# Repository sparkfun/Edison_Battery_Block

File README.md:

SparkFun Block for Intel Edison - Battery/Power
=================================================

[*SparkFun Block for Intel Edison - Battery/Power (DEV-13037)*](https://www.sparkfun.com/products/13037)

Go wireless with Edison!  
The Battery board brings a single cell LiPo Charger and 400mah battery to power an Intel Edision and expansion cards.  
The Battery board can be used with an external battery to increase runtime.  Simply plug in a micro USB cable to charge.  
The power switch removes the battery from the Edison while allowing it to charge via the microUSB cable.

Repository Contents
-------------------
* **/Hardware** - Eagle design files (.brd, .sch)
* **/Production** - Production panel files (.brd)

Documentation
--------------
* **[Hookup Guide](https://learn.sparkfun.com/tutorials/sparkfun-blocks-for-intel-edison---battery-block)** - Basic hookup guide for the battery/power block.
* **[SparkFun Fritzing repo](https://github.com/sparkfun/Fritzing_Parts)** - Fritzing diagrams for SparkFun products.
* **[SparkFun 3D Model repo](https://github.com/sparkfun/3D_Models)** - 3D models of SparkFun products. 

Product Versions
----------------
* [Battery Block](https://www.sparkfun.com/products/13037)- Battery block.
* [Power Block](https://www.sparkfun.com/products/13727)- Battery block without lipo battery installed. 

License Information
-------------------

This product is _**open source**_! 

Please review the LICENSE.md file for license information. 

If you have any questions or concerns on licensing, please contact techsupport@sparkfun.com.

Distributed as-is; no warranty is given.

- Your friends at SparkFun.

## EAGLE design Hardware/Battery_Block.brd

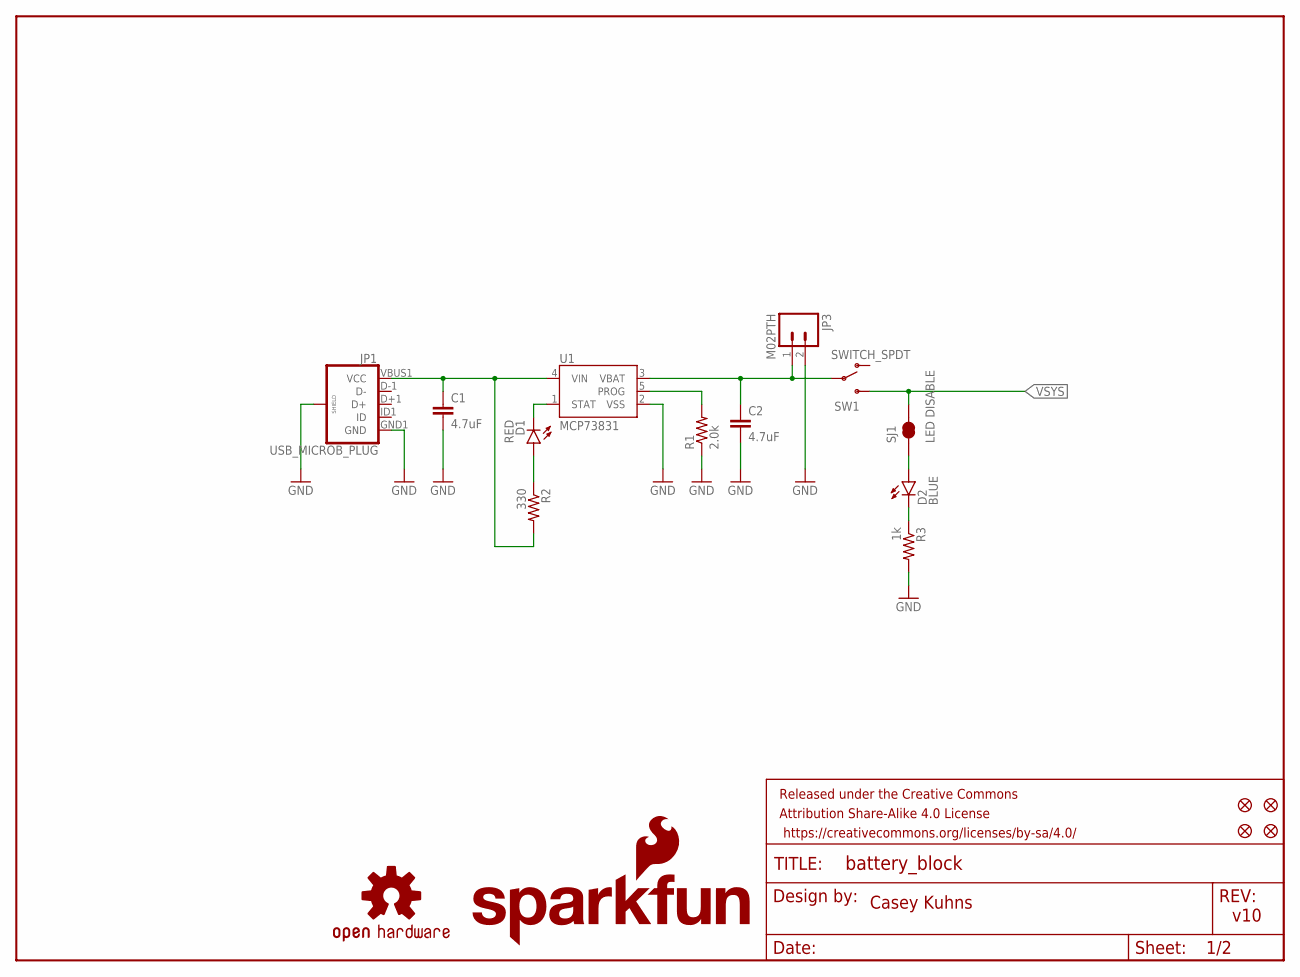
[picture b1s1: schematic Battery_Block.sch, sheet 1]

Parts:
C1, C2: 4.7uF; 0603-CAP
D1: RED; LED-0603
D2: BLUE; LED-0603
FID1, FID2, FID3, FID4: FIDUCIAL1X2; FIDUCIAL-1X2
FRAME1: FRAME-LETTER; CREATIVE_COMMONS
JP1: USB_MICROB_PLUG; USB-B-MICRO-SMD_V03
JP3: M02PTH; 1X02
LOGO1: OSHW-LOGOS; OSHW-LOGO-S
LOGO4: SFE_LOGO_NAME_FLAME.1_INCH; SFE_LOGO_NAME_FLAME_.1
R1: 2.0k; 0603-RES
R2: 330; 0603-RES
R3: 1k; 0603-RES
SJ1: LED DISABLE; PAD-JUMPER-2-NC_BY_TRACE_YES_SILK
SW1: SWITCH_SPDT; KPS-1290
U1: MCP73831; SOT23-5

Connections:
GND: C1.2, C2.2, JP1.GND1 (GND), JP1.SHIELD1 (SHIELD), JP1.SHIELD2 (SHIELD), JP1.SHIELD3 (SHIELD), JP3.2, R1.1, R3.2, U1.2 (VSS); also elsewhere on the board
unnamed: D2.C, R3.1
unnamed: R1.2, U1.5 (PROG)
unnamed: D1.A, R2.1
unnamed: D1.C, U1.1 (STAT)
unnamed: D2.A, SJ1.1
VBAT: C2.1, JP3.1, SW1.P, U1.3 (VBAT)
VIN: C1.1, JP1.VBUS1 (VCC), R2.2, U1.4 (VIN)
VSYS: SJ1.2, SW1.S; also elsewhere on the board

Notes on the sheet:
Casey Kuhns
v10

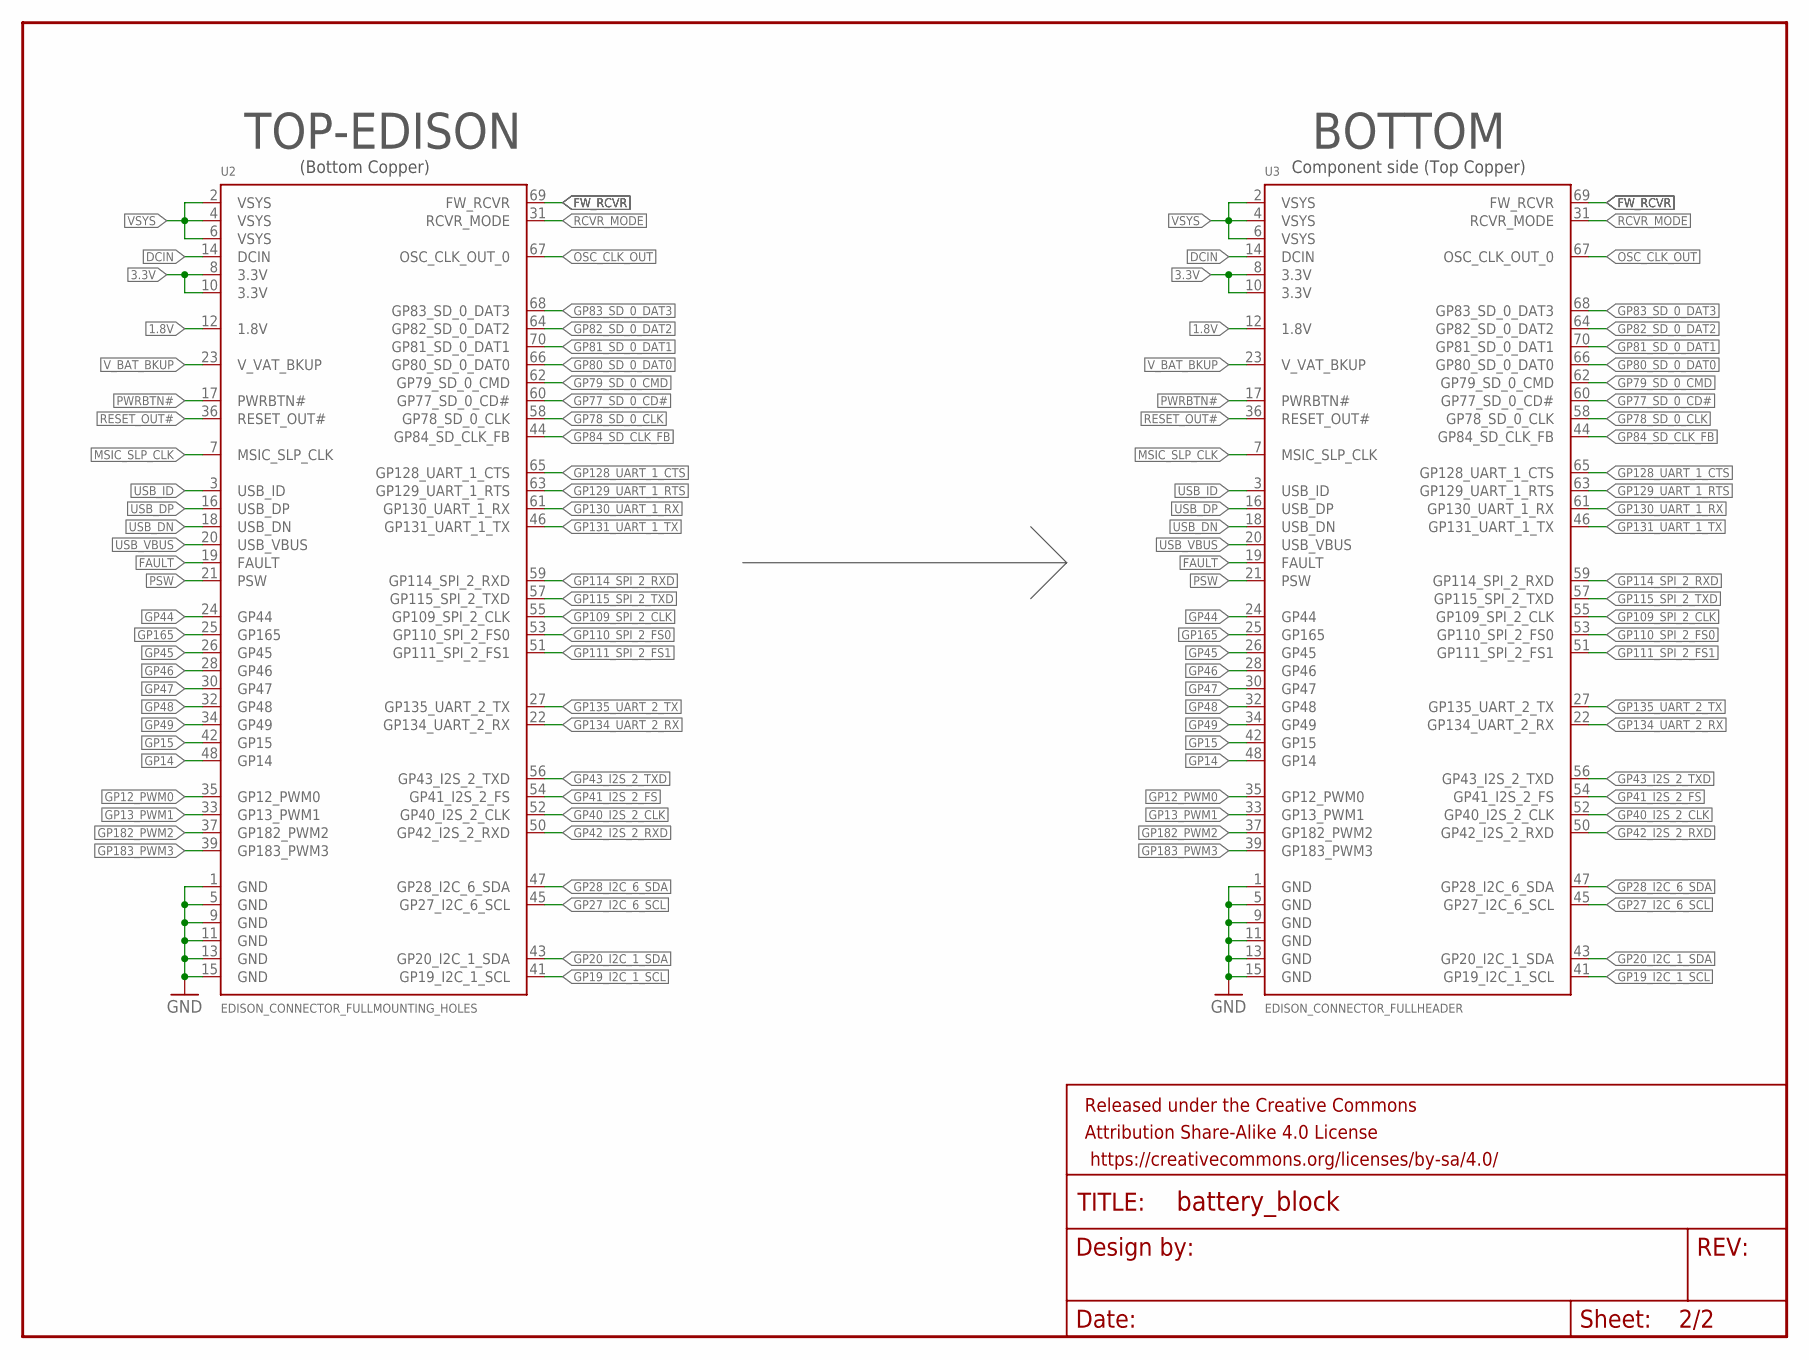
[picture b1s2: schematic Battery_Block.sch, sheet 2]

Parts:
FRAME2: FRAME-LETTER; CREATIVE_COMMONS
U2: EDISON_CONNECTOR_FULLMOUNTING_HOLES; EDISON_DAUGHTER
U3: EDISON_CONNECTOR_FULLHEADER; DF40C-70DP-0.4(51)

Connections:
1.8V: U2.12 (1.8V), U3.12 (1.8V)
3.3V: U2.8 (3.3V), U2.10 (3.3V), U3.8 (3.3V), U3.10 (3.3V)
DCIN: U2.14 (DCIN), U3.14 (DCIN)
FAULT: U2.19 (FAULT), U3.19 (FAULT)
FW_RCVR: U2.69 (FW_RCVR), U3.69 (FW_RCVR)
GND: U2.1 (GND), U2.5 (GND), U2.9 (GND), U2.11 (GND), U2.13 (GND), U2.15 (GND), U3.1 (GND), U3.5 (GND), U3.9 (GND), U3.11 (GND), U3.13 (GND), U3.15 (GND); also elsewhere on the board
GP12_PWM0: U2.35 (GP12_PWM0), U3.35 (GP12_PWM0)
GP13_PWM1: U2.33 (GP13_PWM1), U3.33 (GP13_PWM1)
GP14: U2.48 (GP14), U3.48 (GP14)
GP15: U2.42 (GP15), U3.42 (GP15)
GP19_I2C_1_SCL: U2.41 (GP19_I2C_1_SCL), U3.41 (GP19_I2C_1_SCL)
GP20_I2C_1_SDA: U2.43 (GP20_I2C_1_SDA), U3.43 (GP20_I2C_1_SDA)
GP27_I2C_6_SCL: U2.45 (GP27_I2C_6_SCL), U3.45 (GP27_I2C_6_SCL)
GP28_I2C_6_SDA: U2.47 (GP28_I2C_6_SDA), U3.47 (GP28_I2C_6_SDA)
GP40_I2S_2_CLK: U2.52 (GP40_I2S_2_CLK), U3.52 (GP40_I2S_2_CLK)
GP41_I2S_2_FS: U2.54 (GP41_I2S_2_FS), U3.54 (GP41_I2S_2_FS)
GP42_I2S_2_RXD: U2.50 (GP42_I2S_2_RXD), U3.50 (GP42_I2S_2_RXD)
GP43_I2S_2_TXD: U2.56 (GP43_I2S_2_TXD), U3.56 (GP43_I2S_2_TXD)
GP44: U2.24 (GP44), U3.24 (GP44)
GP45: U2.26 (GP45), U3.26 (GP45)
GP46: U2.28 (GP46), U3.28 (GP46)
GP47: U2.30 (GP47), U3.30 (GP47)
GP48: U2.32 (GP48), U3.32 (GP48)
GP49: U2.34 (GP49), U3.34 (GP49)
GP77_SD_0_CD#: U2.60 (GP77_SD_0_CD#), U3.60 (GP77_SD_0_CD#)
GP78_SD_0_CLK: U2.58 (GP78_SD_0_CLK), U3.58 (GP78_SD_0_CLK)
GP79_SD_0_CMD: U2.62 (GP79_SD_0_CMD), U3.62 (GP79_SD_0_CMD)
GP80_SD_0_DAT0: U2.66 (GP80_SD_0_DAT0), U3.66 (GP80_SD_0_DAT0)
GP81_SD_0_DAT1: U2.70 (GP81_SD_0_DAT1), U3.70 (GP81_SD_0_DAT1)
GP82_SD_0_DAT2: U2.64 (GP82_SD_0_DAT2), U3.64 (GP82_SD_0_DAT2)
GP83_SD_0_DAT3: U2.68 (GP83_SD_0_DAT3), U3.68 (GP83_SD_0_DAT3)
GP84_SD_CLK_FB: U2.44 (GP84_SD_CLK_FB), U3.44 (GP84_SD_CLK_FB)
GP109_SPI_2_CLK: U2.55 (GP109_SPI_2_CLK), U3.55 (GP109_SPI_2_CLK)
GP110_SPI_2_FS0: U2.53 (GP110_SPI_2_FS0), U3.53 (GP110_SPI_2_FS0)
GP111_SPI_2_FS1: U2.51 (GP111_SPI_2_FS1), U3.51 (GP111_SPI_2_FS1)
GP114_SPI_2_RXD: U2.59 (GP114_SPI_2_RXD), U3.59 (GP114_SPI_2_RXD)
GP115_SPI_2_TXD: U2.57 (GP115_SPI_2_TXD), U3.57 (GP115_SPI_2_TXD)
GP128_UART_1_CTS: U2.65 (GP128_UART_1_CTS), U3.65 (GP128_UART_1_CTS)
GP129_UART_1_RTS: U2.63 (GP129_UART_1_RTS), U3.63 (GP129_UART_1_RTS)
GP130_UART_1_RX: U2.61 (GP130_UART_1_RX), U3.61 (GP130_UART_1_RX)
GP131_UART_1_TX: U2.46 (GP131_UART_1_TX), U3.46 (GP131_UART_1_TX)
GP134_UART_2_RX: U2.22 (GP134_UART_2_RX), U3.22 (GP134_UART_2_RX)
GP135_UART_2_TX: U2.27 (GP135_UART_2_TX), U3.27 (GP135_UART_2_TX)
GP165: U2.25 (GP165), U3.25 (GP165)
GP182_PWM2: U2.37 (GP182_PWM2), U3.37 (GP182_PWM2)
GP183_PWM3: U2.39 (GP183_PWM3), U3.39 (GP183_PWM3)
MSIC_SLP_CLK: U2.7 (MSIC_SLP_CLK), U3.7 (MSIC_SLP_CLK)
OSC_CLK_OUT: U2.67 (OSC_CLK_OUT_0), U3.67 (OSC_CLK_OUT_0)
PSW: U2.21 (PSW), U3.21 (PSW)
PWRBTN#: U2.17 (PWRBTN#), U3.17 (PWRBTN#)
RCVR_MODE: U2.31 (RCVR_MODE), U3.31 (RCVR_MODE)
RESET_OUT#: U2.36 (RESET_OUT#), U3.36 (RESET_OUT#)
USB_DN: U2.18 (USB_DN), U3.18 (USB_DN)
USB_DP: U2.16 (USB_DP), U3.16 (USB_DP)
USB_ID: U2.3 (USB_ID), U3.3 (USB_ID)
USB_VBUS: U2.20 (USB_VBUS), U3.20 (USB_VBUS)
VSYS: U2.2 (VSYS), U2.4 (VSYS), U2.6 (VSYS), U3.2 (VSYS), U3.4 (VSYS), U3.6 (VSYS); also elsewhere on the board
V_BAT_BKUP: U2.23 (V_VAT_BKUP), U3.23 (V_VAT_BKUP)

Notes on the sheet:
TOP-EDISON
BOTTOM
Component side (Top Copper)
(Bottom Copper)

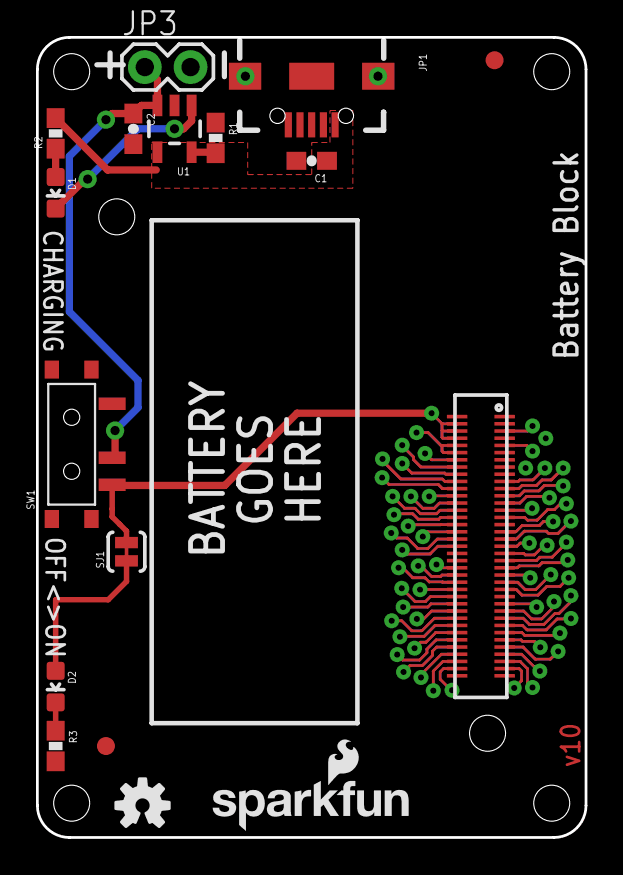
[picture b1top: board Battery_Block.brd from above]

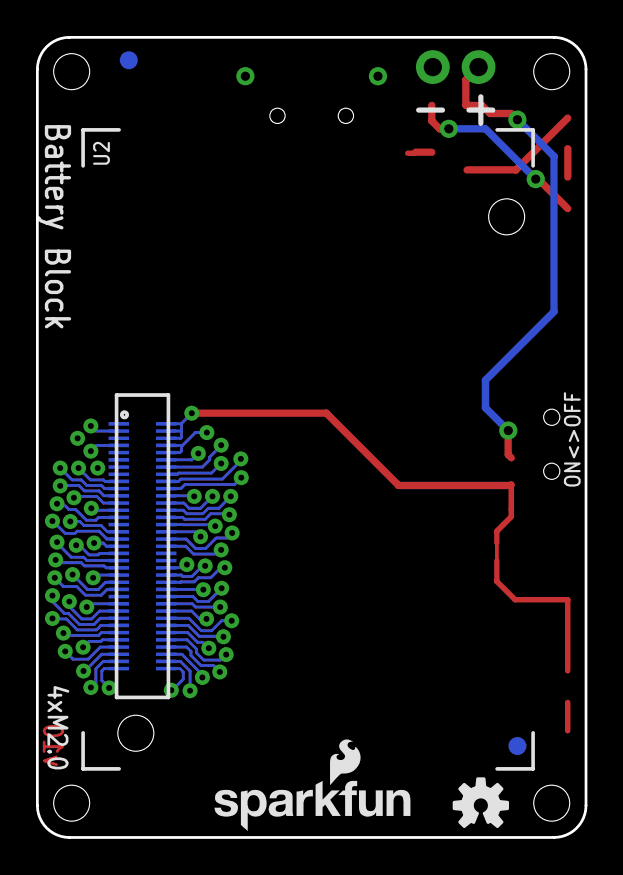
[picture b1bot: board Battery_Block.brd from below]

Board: 2 copper layers, 30.5 x 44.5 mm, 24 parts (6 on the bottom side), 65 nets.

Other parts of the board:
LOGO2: OSHW-LOGOS; OSHW-LOGO-S
LOGO3: SFE_LOGO_NAME_FLAME.1_INCH; SFE_LOGO_NAME_FLAME_.1

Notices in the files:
parts and their libraries:
SparkFun-Aesthetics: Licensing: Creative Commons ShareAlike 4.0 International - https://creativecommons.org/licenses/by-sa/4.0
SparkFun-Aesthetics: Released under the Creative Commons Attribution Share-Alike 4.0 License
SparkFun-Aesthetics: https://creativecommons.org/licenses/by-sa/4.0
